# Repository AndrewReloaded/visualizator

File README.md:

# Visualizator
Inspired by https://www.youtube.com/watch?v=BRrXSYXCs88&t=329s

# Original project
https://github.com/nootropicdesign/lumazoid

https://nootropicdesign.com/lumazoid/

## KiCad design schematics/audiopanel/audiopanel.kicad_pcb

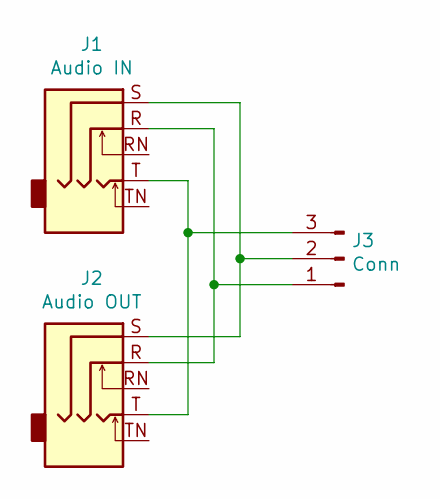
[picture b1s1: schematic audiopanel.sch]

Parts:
J1: Audio IN; Jack_3.5mm_Ledino_KB3SPRS_Horizontal
J2: Audio OUT; Jack_3.5mm_Ledino_KB3SPRS_Horizontal
J3: Conn; SolderWirePad_1x03_P3.175mm_Drill1mm

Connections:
unnamed: J1.R, J2.R, J3.1
unnamed: J1.S, J2.S, J3.2
unnamed: J1.T, J2.T, J3.3

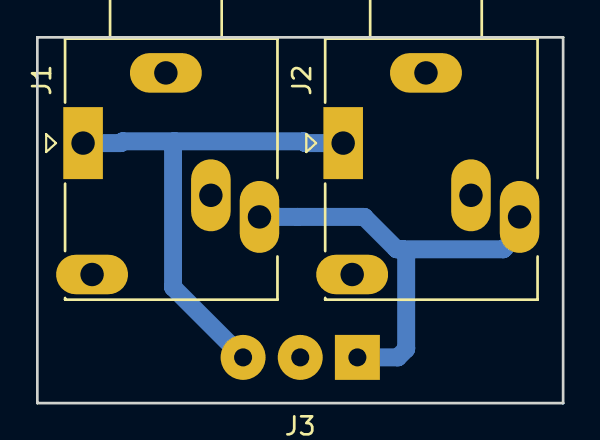
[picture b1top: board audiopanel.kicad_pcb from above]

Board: 2 copper layers, 29.2 x 20.3 mm, 3 parts (0 on the bottom side), 3 nets.

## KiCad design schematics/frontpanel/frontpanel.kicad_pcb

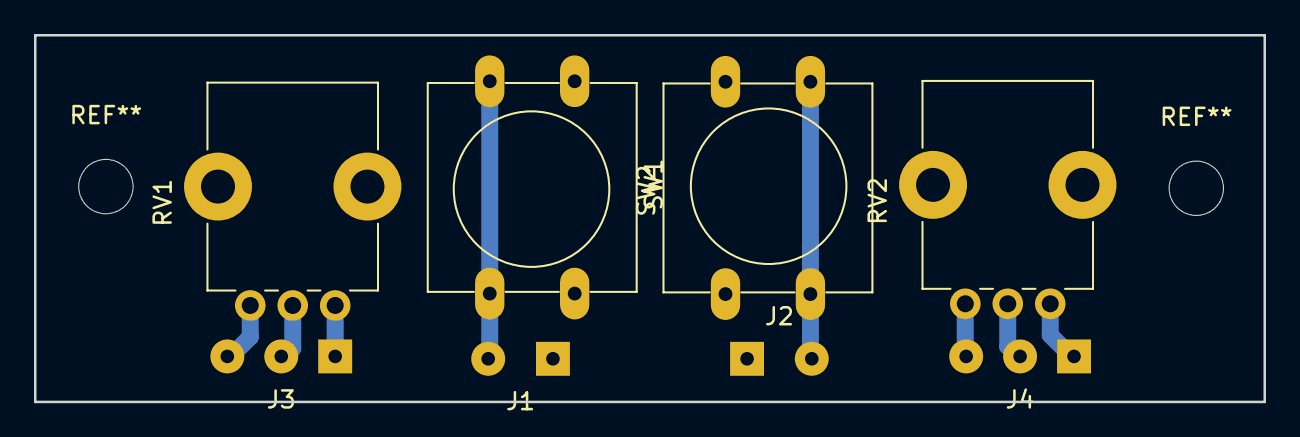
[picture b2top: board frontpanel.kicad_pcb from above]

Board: 2 copper layers, 72.4 x 21.6 mm, 8 parts (0 on the bottom side), 9 nets.

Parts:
J1, J2: Conn_01x02_Male; SolderWirePad_1x02_P3.81mm_Drill0.8mm
J3, J4: Conn_01x03_Male; SolderWirePad_1x03_P3.175mm_Drill0.8mm
RV1, RV2: R_POT; Potentiometer_Alps_RK09K_Single_Vertical
SW1, SW2: SW_Push; SW_PUSH-12mm

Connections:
unnamed: J1.1, J2.1, SW1.1, SW2.1
unnamed: J1.2, SW1.2
unnamed: J2.2, SW2.2
unnamed: J3.1, RV1.1
unnamed: J3.2, RV1.2
unnamed: J3.3, RV1.3
unnamed: J4.1, RV2.1
unnamed: J4.2, RV2.2
unnamed: J4.3, RV2.3

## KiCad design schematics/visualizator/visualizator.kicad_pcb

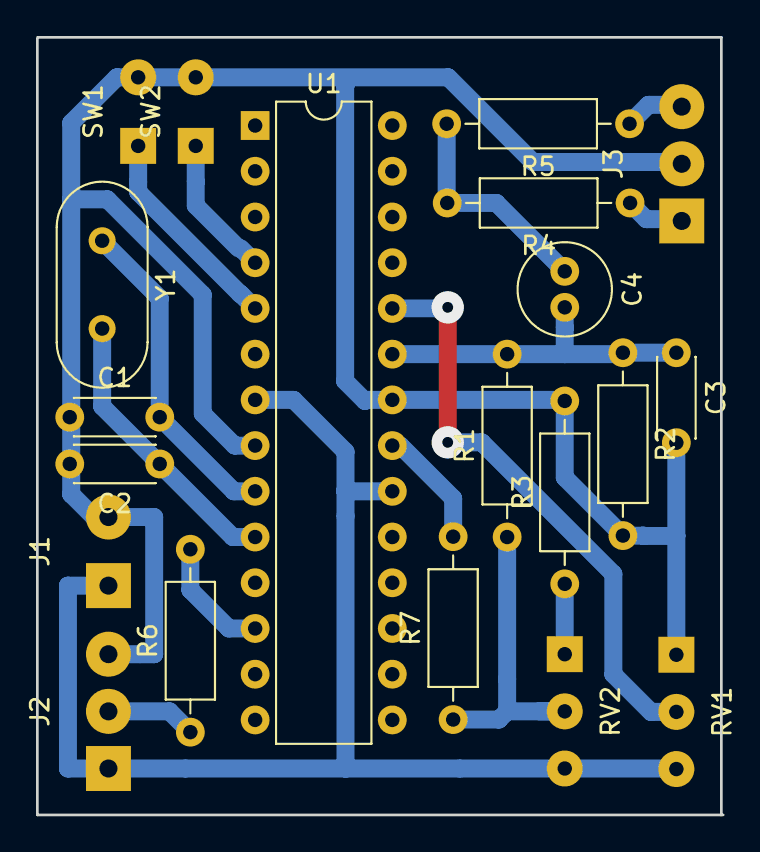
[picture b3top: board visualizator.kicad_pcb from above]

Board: 2 copper layers, 38.1 x 43.2 mm, 20 parts (0 on the bottom side), 16 nets.

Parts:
C1, C2: 22pF; C_Disc_D4.3mm_W1.9mm_P5.00mm
C3: 0,1uF; C_Disc_D4.3mm_W1.9mm_P5.00mm
C4: 10uF; C_Radial_D5.0mm_H11.0mm_P2.00mm
J1: 5V; SolderWirePad_1x02_P3.81mm_Drill1mm
J2: WS2812; SolderWirePad_1x03_P3.175mm_Drill1mm
J3: Audio; SolderWirePad_1x03_P3.175mm_Drill1mm
R1, R2: 100k; R_Axial_DIN0207_L6.3mm_D2.5mm_P10.16mm_Horizontal
R3, R7: 2k; R_Axial_DIN0207_L6.3mm_D2.5mm_P10.16mm_Horizontal
R4, R5: 2*k; R_Axial_DIN0207_L6.3mm_D2.5mm_P10.16mm_Horizontal
R6: 220; R_Axial_DIN0207_L6.3mm_D2.5mm_P10.16mm_Horizontal
RV1: 10k; SolderWirePad_1x03_P3.175mm_Drill0.8mm
RV2: 50k; SolderWirePad_1x03_P3.175mm_Drill0.8mm
SW1: COLOR; SolderWirePad_1x02_P3.81mm_Drill0.8mm
SW2: PATTERN; SolderWirePad_1x02_P3.81mm_Drill0.8mm
U1: ATmega328-16PU; DIP-28_W7.62mm
Y1: 16MHz; Crystal_HC49-4H_Vertical

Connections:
unnamed: C1.1, C2.2, C3.2, J1.2, J2.3, J3.2, R2.2, R3.2, RV1.1, SW1.2, SW2.2, U1.8, U1.22
unnamed: C1.2, U1.9, Y1.1
unnamed: C2.1, U1.10, Y1.2
unnamed: C3.1, C4.2, R1.2, R2.1, U1.23
unnamed: C4.1, R4.2, R5.2
unnamed: J1.1, J2.1, RV1.3, RV2.3, U1.7, U1.20
unnamed: J2.2, R6.1
unnamed: J3.1, R4.1
unnamed: J3.3, R5.1
unnamed: R1.1, R7.1, RV2.2
unnamed: R3.1, RV2.1
unnamed: R6.2, U1.12
unnamed: R7.2, U1.21
unnamed: RV1.2, U1.24
unnamed: SW1.1, U1.5
unnamed: SW2.1, U1.4

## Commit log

2018-12-16 scetch added
2018-12-16 redme updated
2018-12-16 Changed drsign rules
2018-12-16 Added schematics and PCB from KiCAD
2018-12-17 PCB updated
2018-12-20 Added v2 PCB. Added front panel for v1 PCB
2018-12-21 Updated front panel PCB for v1
2018-12-21 Changed reistors
2018-12-21 updated a print version of the PCB
2018-12-21 Added a print version of the front panel PCB Added a 3D rendered PCB view
2018-12-23 Updated PCB
2019-01-20 PCBs updated
2019-01-20 updated negative PCB images
2019-01-21 Updated PCB image files
2019-01-27 Added PCB for 3,5 mm audio connectors
2019-01-27 Updated PCB for audio connectors
2019-01-27 Outdated PCBs removed
